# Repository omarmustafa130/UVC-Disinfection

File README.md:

# Hardware & PCB -- Scroll down for software part
The board is very, very compact, at just 21mm x 35mm, designed as a double-layer PCB, and integrates a smart power control system alongside motion-based UVC LED activation, and is able to last +30 days on battery.

The board features:
1- MCU: STM32L031K6T – a low-power Cortex-M0+ MCU to handle control logic efficiently.

2- Motion Sensing: LSM6DS3 – a 3D accelerometer & gyroscope determines orientation to activate the correct UVC LED.

3- UVC LEDs: 2x 254nm LEDs (23mW, 150mA) – ensure effective disinfection, switching every 60 minutes for 90 seconds based on orientation.

4- Power Management:
- L7BM06CDT (6V regulator)
- L78L33ACUTR (3.3V regulator) for the MCU
- MCP73831-2-MC (Li-ion charging IC) for battery management

5- User Interface & Control:
- Status LEDs (2x) & Power LED (1x) for feedback.
- A user button for additional interaction.
- Power Button using D Flip-Flop (74HC74) – holds power after a 5-second press, controlled via an RC delay circuit.
Instead of an always-on MCU (to save the battery), the device remains completely powered off until the user presses the power button for 5 seconds.
Uses a D flip-flop latch circuit with an RC network to ensure accidental presses don’t turn it on.
- ON/OFF Switch for direct power control when needed.
- 4-pin JST connector for ST-LINK interface
- Two 2-pin JST connector for the batteries and their charger

# Software 
# **STM32 UVC LED Control with Low Power Mode**

## **Overview**

This project controls **UVC LEDs** based on the device's **orientation**, using an **LSM6DS33 accelerometer**. It follows a power-efficient cycle:

1. **Waits 30 seconds** before activating.
2. **Blinks an indicator LED for 5 seconds**.
3. **Determines the orientation** of the device.
4. **Activates the appropriate UVC LED** for **90 seconds** while the indicator LED blinks.
5. **Turns OFF all LEDs** after operation.
6. **Enters deep sleep mode (STOP mode) for 1 hour** to conserve power.

The system **wakes up automatically after 1 hour** and repeats the cycle.

---

## **Hardware Requirements**

To test this code, you need:

- **STM32 (e.g., STM32F103RB Nucleo or similar)**
- **LSM6DS33 Accelerometer (I2C)**
- **UVC LEDs** (connected to GPIOA)
- **Indicator LEDs**
- **Power supply** (battery or USB)

---

## **Pin Configuration**

| **Component**            | **GPIO Pin** | **Port** |
| ------------------------ | ------------ | -------- |
| **Top UVC LED**          | `GPIO_PIN_0` | `GPIOA`  |
| **Bottom UVC LED**       | `GPIO_PIN_1` | `GPIOA`  |
| **Top Indicator LED**    | `GPIO_PIN_3` | `GPIOA`  |
| **Bottom Indicator LED** | `GPIO_PIN_7` | `GPIOA`  |
| **I2C SDA**              | `GPIO_PIN_9` | `GPIOB`  |
| **I2C SCL**              | `GPIO_PIN_8` | `GPIOB`  |

---

## **Project Structure**

```
/STM32_UVC_LowPower/
│── Core/
│   ├── Inc/
│   │   ├── main.h
│   │   ├── LSM6DS33.h
│   ├── Src/
│   │   ├── main.c
│   │   ├── LSM6DS33.c
│── README.md
```

---

## **How It Works**

### **1- Initialization**

- **STM32 peripherals** (GPIO, I2C, System Clock) are initialized.
- **LSM6DS33 accelerometer** is configured.

### **2- LED Activation Sequence**

- **Waits 30 seconds** after boot.
- **Blinks indicator LED** for **5 seconds**.
- **Reads orientation** from **LSM6DS33**.
- **Turns ON the correct UVC LED** (based on orientation).
- **Blinks indicator LED for 90 seconds** while UVC LED is ON.
- **Turns OFF all LEDs** after the cycle.

### **3- Power Saving Mode**

- **Enters STOP mode (Deep Sleep) for 1 hour.**
- **Disables unused peripherals (GPIO, I2C) before sleep.**
- **Resumes peripherals after waking up.**
- **Restores system clock to normal operation.**
- **Repeats the process indefinitely.**

---

## **How to Test**

### **🔹 Option 1: Flash and Run**

1. **Flash the firmware** using STM32CubeProgrammer or an ST-Link.
2. **Connect serial monitor** to see debug messages (optional).
3. **Observe LED behavior**:
   - Indicator LED blinks for 5 seconds.
   - UVC LED turns ON based on orientation.
   - Indicator LED blinks for 90 seconds while UVC is ON.
   - After LEDs turn OFF, the system **enters low-power mode for 1 hour**.
   - The process repeats.

### **🔹 Option 2: Modify Sleep Duration for Testing**

Since **1-hour sleep is long**, modify `enter_low_power_mode()` for quicker tests:

```c
while ((HAL_GetTick() - tickstart) < 30000)  // 30 seconds instead of 1 hour
```

This allows testing the **wake-up cycle faster**.

---

## **Power Consumption & Optimization**

| **Mode**                                     | **Power Consumption** |
| -------------------------------------------- | --------------------- |
| **Active (LEDs ON, CPU running)**            | \~20mA                |
| **Deep Sleep (STOP Mode, LEDs OFF)**         | **\~200-500µA**       |
| **Estimated Battery Life (1000mAh battery)** | \~66 Days             |

🔹 **Further Power Optimizations:**

- Use **Standby Mode (\~1µA) instead of STOP mode**.
- **Disable more peripherals** (e.g., ADC, UART, timers).
- Use an **RTC wake-up instead of HAL\_GetTick().**

---

## **Troubleshooting**

### **1- STM32 Doesn’t Wake Up**

**Solution: Ensure SysTick timer is active**

- **HAL\_SuspendTick()** prevents unwanted wake-ups.
- **`SCB->SCR |= SCB_SCR_SLEEPDEEP_Msk;`** is required for STOP mode.

### **2- I2C Stops Working After Wake-up**

**Solution: Reset I2C after STOP mode**

```c
__HAL_RCC_I2C1_FORCE_RESET();
HAL_Delay(10);
__HAL_RCC_I2C1_RELEASE_RESET();
MX_I2C1_Init();
LSM6DS33_init();
```

### **3- UVC LED Doesn't Turn ON**

**Solution: Check orientation detection**

- Add debug prints:

```c
printf("Orientation: %d
", orientation);
```

---

## **Additional Resources**

- [STM32 HAL Documentation](https://www.st.com/en/embedded-software/stm32cube-mcu-packages.html)
- [LSM6DS33 Datasheet](https://www.st.com/resource/en/datasheet/lsm6ds33.pdf)
- [Low Power Modes on STM32](https://www.st.com/resource/en/application_note/an4830-lowpower-modes-for-stm32-mcus.pdf)

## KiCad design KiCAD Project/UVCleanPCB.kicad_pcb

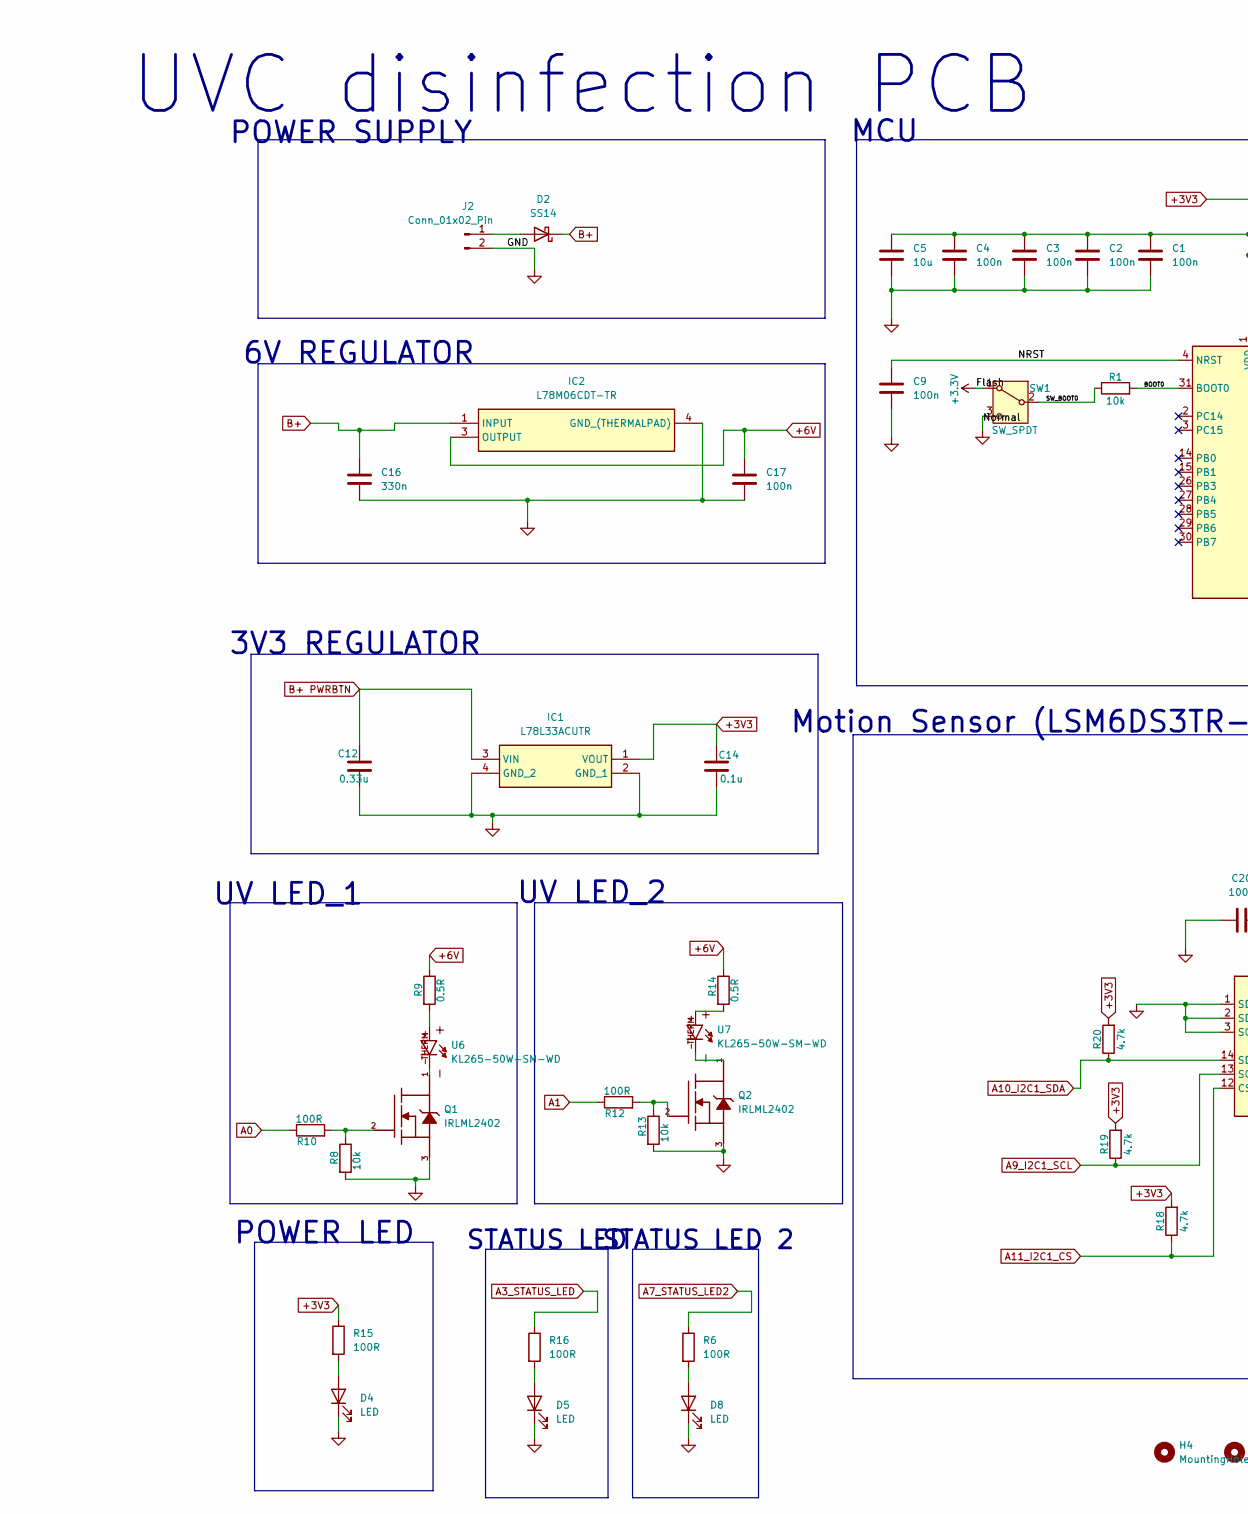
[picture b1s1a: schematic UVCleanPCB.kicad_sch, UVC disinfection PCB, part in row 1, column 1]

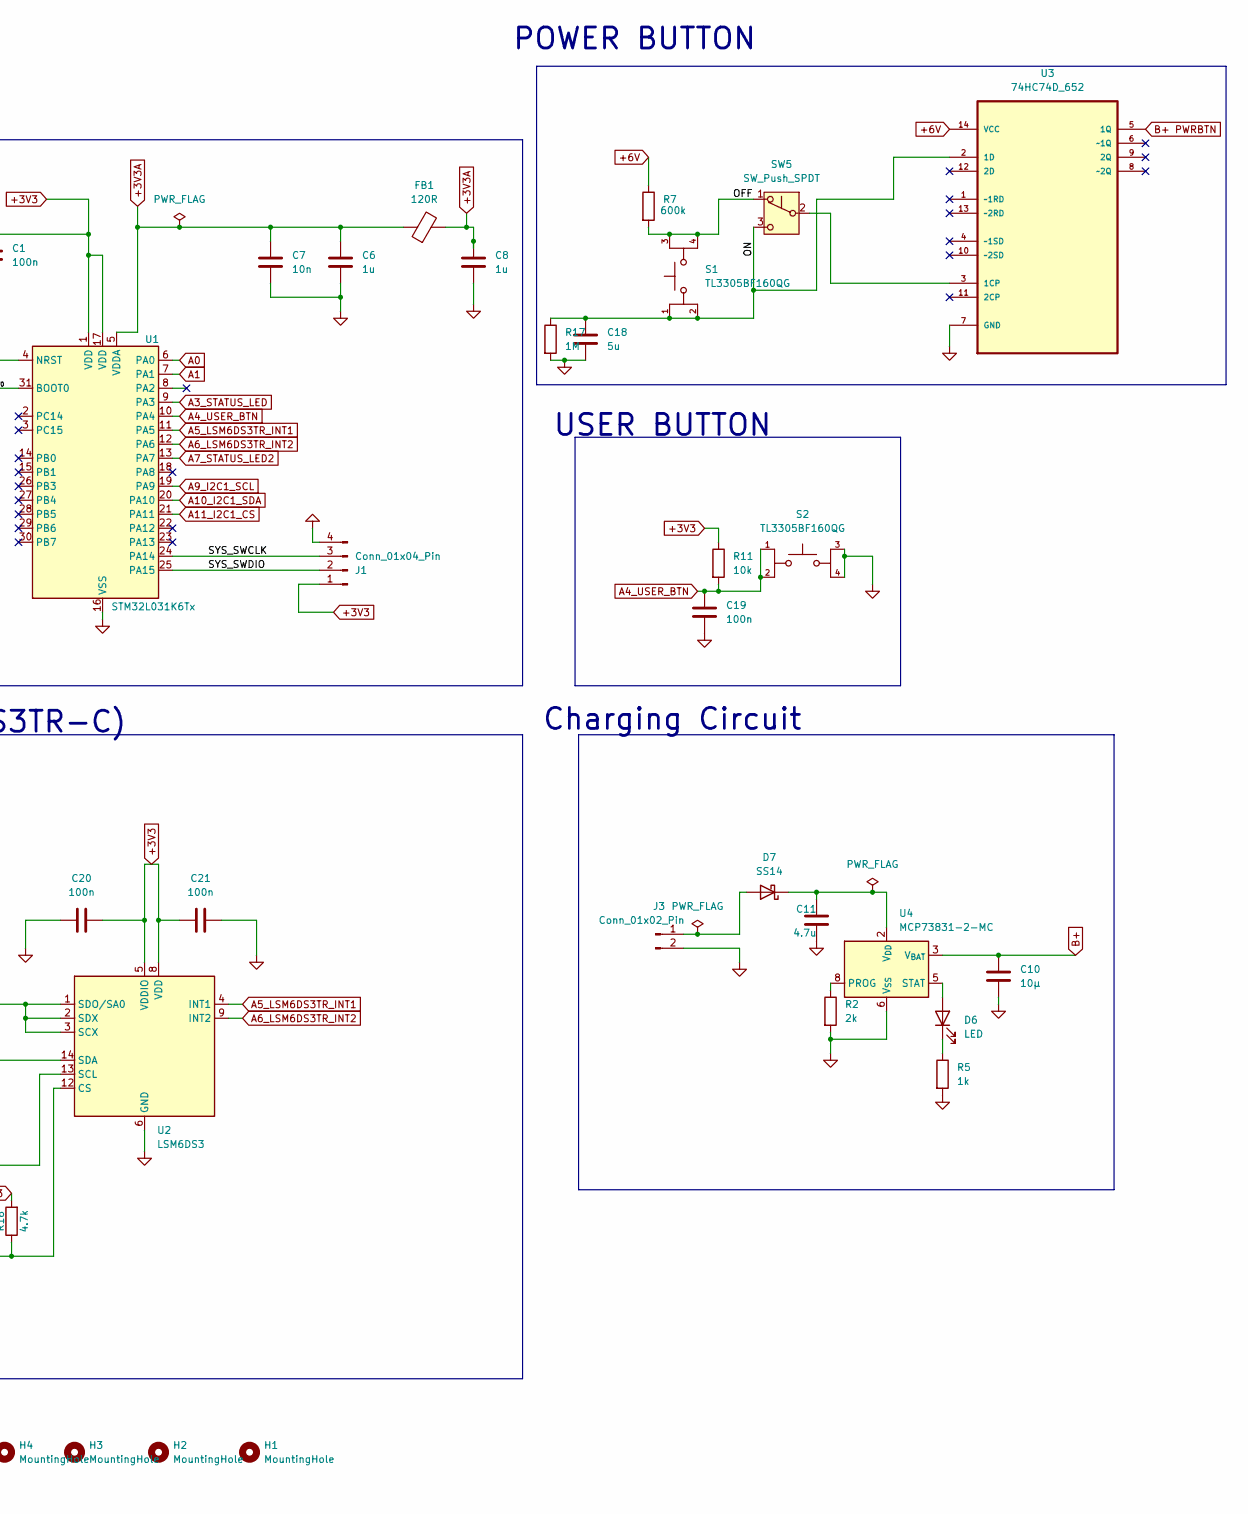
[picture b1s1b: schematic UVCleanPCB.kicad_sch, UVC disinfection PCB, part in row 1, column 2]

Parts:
C1, C2, C3, C4, C9, C19, C20, C21: 100n; C_0402_1005Metric
C5: 10u; C_0603_1608Metric
C6, C8: 1u; C_0402_1005Metric
C7: 10n; C_0402_1005Metric
C10: 10µ; C_0402_1005Metric
C11: 4.7u; C_0402_1005Metric
C12: 0.33u; C_1206_3216Metric
C14: 0.1u; C_1206_3216Metric
C16: 330n; C_0603_1608Metric
C17: 100n; C_0603_1608Metric
C18: 5u; C_0805_2012Metric
D2, D7: SS14; D_SMA
D4, D5, D8: LED; LED_0603_1608Metric
D6: LED; LED_0402_1005Metric
FB1: 120R; L_0603_1608Metric
H1, H2, H3, H4: MountingHole; MountingHole_2.1mm
IC1: L78L33ACUTR; LDK320ADU30R; Mouser Part Number 511-L78L33ACU
IC2: L78M06CDT-TR; TO228P972X240-3N; Mouser Part Number 511-L78M06CDT-TR
J1: Conn_01x04_Pin; JST_EH_B4B-EH-A_1x04_P2.50mm_Vertical
J2, J3: Conn_01x02_Pin; JST_EH_B2B-EH-A_1x02_P2.50mm_Vertical
Q1, Q2: IRLML2402; SOT-23
R1, R11: 10k; R_0402_1005Metric
R2: 2k; R_0402_1005Metric
R5: 1k; R_0402_1005Metric
R6, R15, R16: 100R; R_0402_1005Metric
R7: 600k; R_0603_1608Metric
R8, R13: 10k; R_0603_1608Metric
R9, R14: 0.5R; R_0603_1608Metric
R10, R12: 100R; R_0603_1608Metric
R17: 1M; R_0603_1608Metric
R18, R19, R20: 4.7k; R_0402_1005Metric
S1, S2: TL3305BF160QG; SW_TL3305BF160QG; PARTREV C
SW1: SW_SPDT; SW_SPDT_PCM12
SW5: SW_Push_SPDT; SW_SPDT_PCM12
U1: STM32L031K6Tx; LQFP-32_7x7mm_P0.8mm
U2: LSM6DS3; LGA-14_3x2.5mm_P0.5mm_LayoutBorder3x4y
U3: 74HC74D_652; SOIC127P600X175-14N; MPN 74HC74D,652
U4: MCP73831-2-MC; SOT-23-8
U6, U7: KL265-50W-SM-WD; 3535

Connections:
+3.3V: SW1.1 (A)
+3V3: C1.1, C2.1, C3.1, C4.1, C5.1, C14.1, C20.2, C21.1, IC1.1 (VOUT), J1.1, R11.1, R15.1, R18.2, R19.2, R20.2, U1.1 (VDD), U1.17 (VDD), U2.5 (VDDIO), U2.8 (VDD)
+3V3A: C6.1, C7.1, C8.1, FB1.1, FB1.2, U1.5 (VDDA)
+6V: C17.1, IC2.3 (OUTPUT), R7.1, R9.1, R14.1, U3.14 (VCC)
/BOOT0: R1.2, U1.31 (BOOT0)
/NRST: C9.1, U1.4 (NRST)
/OFF: R7.2, S1.3, S1.4, SW5.1 (A)
/ON: C18.1, R17.1, S1.1, S1.2, SW5.3 (C), U3.2 (1D)
/SW_BOOT0: R1.1, SW1.2 (B)
/SYS_SWCLK: J1.3, U1.24 (PA14)
/SYS_SWDIO: J1.2, U1.25 (PA15)
A0: R10.1, U1.6 (PA0)
A1: R12.1, U1.7 (PA1)
A3_STATUS_LED: R16.1, U1.9 (PA3)
A4_USER_BTN: C19.1, R11.2, S2.1, S2.2, U1.10 (PA4)
A5_LSM6DS3TR_INT1: U1.11 (PA5), U2.4 (INT1)
A6_LSM6DS3TR_INT2: U1.12 (PA6), U2.9 (INT2)
A7_STATUS_LED2: R6.1, U1.13 (PA7)
A9_I2C1_SCL: R19.1, U1.19 (PA9), U2.13 (SCL)
A10_I2C1_SDA: R20.1, U1.20 (PA10), U2.14 (SDA)
A11_I2C1_CS: R18.1, U1.21 (PA11), U2.12 (CS)
B+: C10.1, C16.1, D2.1 (K), IC2.1 (INPUT), U4.3 (V_{BAT}), U4.4 (V_{BAT})
B+ PWRBTN: C12.1, IC1.3 (VIN), U3.5 (1Q)
GND: C1.2, C2.2, C3.2, C4.2, C5.2, C6.2, C7.2, C8.2, C9.2, C10.2, C11.2, C12.2, C14.2, C16.2, C17.2, C18.2, C19.2, C20.1, C21.2, D4.1 (K), D5.1 (K), D8.1 (K), IC1.2 (GND_1), IC1.4 (GND_2), IC2.4 (GND_(THERMALPAD)), J1.4, J2.2, J3.2, Q1.3, Q2.3, R2.2, R5.2, R8.2, R13.2, R17.2, S2.3, S2.4, SW1.3 (C), U1.16 (VSS), U1.32 (VSS), U2.1 (SDO/SA0), U2.2 (SDX), U2.3 (SCX), U2.6 (GND), U2.7 (GND), U3.7 (GND), U4.6 (V_{SS})
unnamed: D2.2 (A), J2.1
unnamed: D4.2 (A), R15.2
unnamed: D5.2 (A), R16.2
unnamed: D6.2 (A), U4.5 (STAT)
unnamed: D6.1 (K), R5.1
unnamed: D7.2 (A), J3.1
unnamed: C11.1, D7.1 (K), U4.1 (V_{DD}), U4.2 (V_{DD})
unnamed: D8.2 (A), R6.2
unnamed: Q1.1, U6.-
unnamed: Q1.2, R8.1, R10.2
unnamed: Q2.1, U7.-
unnamed: Q2.2, R12.2, R13.1
unnamed: R9.2, U6.+
unnamed: R14.2, U7.+
unnamed: SW5.2 (B), U3.3 (1CP)
unnamed: R2.1, U4.8 (PROG)

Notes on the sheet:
POWER LED
MCU
UV LED_1
UV LED_2
POWER SUPPLY
6V REGULATOR
USER BUTTON
POWER BUTTON
Charging Circuit
3V3 REGULATOR
Motion Sensor (LSM6DS3TR-C)
STATUS LED 2
UVC disinfection PCB
STATUS LED

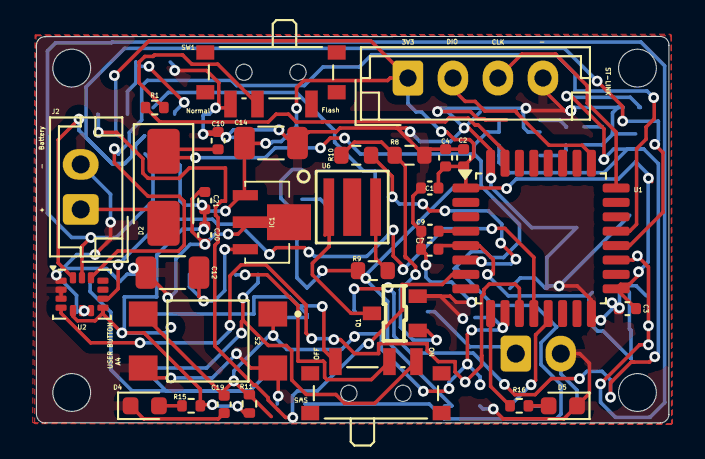
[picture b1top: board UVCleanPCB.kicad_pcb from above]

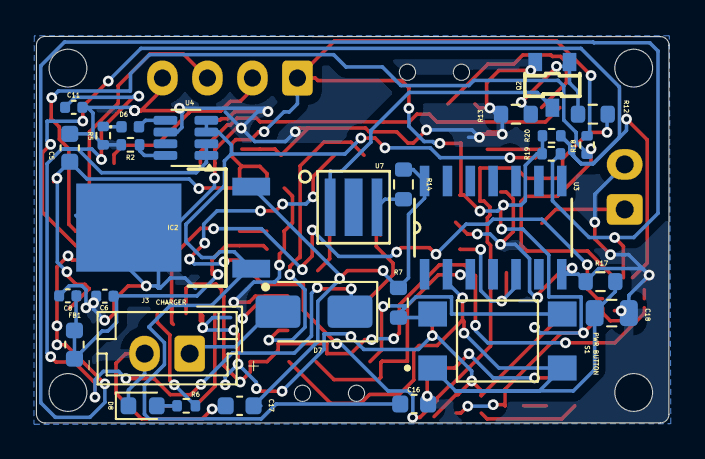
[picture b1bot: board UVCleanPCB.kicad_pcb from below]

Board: 2 copper layers, 35.1 x 21.5 mm, 65 parts (29 on the bottom side), 39 nets.

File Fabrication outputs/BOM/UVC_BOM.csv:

"Id;""Designator"";""Footprint"";""Quantity"";""Designation"";""Supplier and ref"";",,,,,,,
"1;""C10"";""C_0402_1005Metric"";1;""10µ"";;;",,,,,,,
"2;""D4;""LED_0603_1608Metric"";3;""Green LED"";;;",,,,,,,
"3;""D5","D8"";""LED_0603_1608Metric"";3;""Orange LED"";;;",,,,,,
"4;""C9",C2,C3,C19,C1,C20,C4,"C21"";""C_0402_1005Metric"";8;""100n"";;;"
"5;""J1"";""JST_EH_B4B-EH-A_1x04_P2.50mm_Vertical"";1;""Conn_01x04_Pin"";;;",,,,,,,
"6;""Q1","Q2"";""SOT-23"";2;""IRLML2402"";;;",,,,,,
"7;""C12"";""C_1206_3216Metric"";1;""0.33u"";;;",,,,,,,
"8;""R15",R16,"R6"";""R_0402_1005Metric"";3;""100R"";;;",,,,,
"9;""R8","R13"";""R_0603_1608Metric"";2;""10k"";;;",,,,,,
"10;""R11","R1"";""R_0402_1005Metric"";2;""10k"";;;",,,,,,
"11;""SW5"";""SW_SPDT_PCM12"";1;""SW_Push_SPDT"";;;",,,,,,,
"12;""R9","R14"";""R_0603_1608Metric"";2;""0.5R"";;;",,,,,,
"13;""C7"";""C_0402_1005Metric"";1;""10n"";;;",,,,,,,
"14;""D2","D7"";""D_SMA"";2;""SS14"";;;",,,,,,
"15;""SW1"";""SW_SPDT_PCM12"";1;""SW_SPDT"";;;",,,,,,,
"16;""C14"";""C_1206_3216Metric"";1;""0.1u"";;;",,,,,,,
"17;""U1"";""LQFP-32_7x7mm_P0.8mm"";1;""STM32L031K6Tx"";;;",,,,,,,
"18;""S2","S1"";""SW_TL3305BF160QG"";2;""TL3305BF160QG"";;;",,,,,,
"19;""J2","J3"";""JST_EH_B2B-EH-A_1x02_P2.50mm_Vertical"";2;""Conn_01x02_Pin"";;;",,,,,,
"20;""IC1"";""LDK320ADU30R"";1;""L78L33ACUTR"";;;",,,,,,,
"21;""U2"";""LGA-14_3x2.5mm_P0.5mm_LayoutBorder3x4y"";1;""LSM6DS3"";;;",,,,,,,
"22;""R10","R12"";""R_0603_1608Metric"";2;""100R"";;;",,,,,,
"23;""R7"";""R_0603_1608Metric"";1;""600k"";;;",,,,,,,
"24;""C16"";""C_0603_1608Metric"";1;""330n"";;;",,,,,,,
"25;""U3"";""SOIC127P600X175-14N"";1;""74HC74D_652"";;;",,,,,,,
"26;""IC2"";""TO228P972X240-3N"";1;""L78M06CDT-TR"";;;",,,,,,,
"27;""D6"";""LED_0402_1005Metric"";1;""LED"";;;",,,,,,,
"28;""FB1"";""L_0603_1608Metric"";1;""120R"";;;",,,,,,,
"29;""R2"";""R_0402_1005Metric"";1;""2k"";;;",,,,,,,
"30;""C11"";""C_0402_1005Metric"";1;""4.7u"";;;",,,,,,,
"31;""R5"";""R_0402_1005Metric"";1;""1k"";;;",,,,,,,
"32;""U4"";""SOT-23-8"";1;""MCP73831-2-MC"";;;",,,,,,,
"33;""U7","U6"";""3535"";2;""KL265-50W-SM-WD"";;;",,,,,,
"34;""R18",R19,"R20"";""R_0402_1005Metric"";3;""4.7k"";;;",,,,,
"35;""C8","C6"";""C_0402_1005Metric"";2;""1u"";;;",,,,,,
"36;""R17"";""R_0603_1608Metric"";1;""1M"";;;",,,,,,,
"37;""C18"";""C_0805_2012Metric"";1;""5u"";;;",,,,,,,
"38;""C17"";""C_0603_1608Metric"";1;""100n"";;;",,,,,,,
"39;""C5"";""C_0603_1608Metric"";1;""10u"";;;",,,,,,,

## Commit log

2025-02-18 datasheets added
2025-02-18 Schematics V0.1
2025-02-18 Schematics V0.1 PDF
2025-02-19 Additional symbols and footprints
2025-02-19 6.5V regulator
2025-02-21 simulations
2025-02-21 Additional footprints
2025-02-21 Additional datasheets
2025-02-21 Final schematics
2025-02-21 PCB layout
2025-02-25 Project finalized
2025-02-27 UVC Software
